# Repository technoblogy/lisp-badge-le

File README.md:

# Lisp Badge LE
A self-contained low-power computer with its own display and keyboard that you can program in Lisp. It now includes autocomplete, together with the new features in uLisp Release 4.8f.

The files are as follows:

* LispBadgeLE.ino - the uLisp source file for the Lisp Badge LE.
* LispBadgeLE-comments.ino - identical but including comprehensive comments.

Only use one of these files. It should be compiled and uploaded using the Arduino IDE.

For more information see http://www.technoblogy.com/show?3Z2Y.

Note that for consistency with the previous version of the Lisp Badge LE, autocomplete has been assigned to **META-ESC**. If you think that it would be more convenient to have autocomplete on **ESC** and Escape on **META-ESC**, swap the occurrences of '\e' and '\t' in **Keymap[]** before uploading uLisp.

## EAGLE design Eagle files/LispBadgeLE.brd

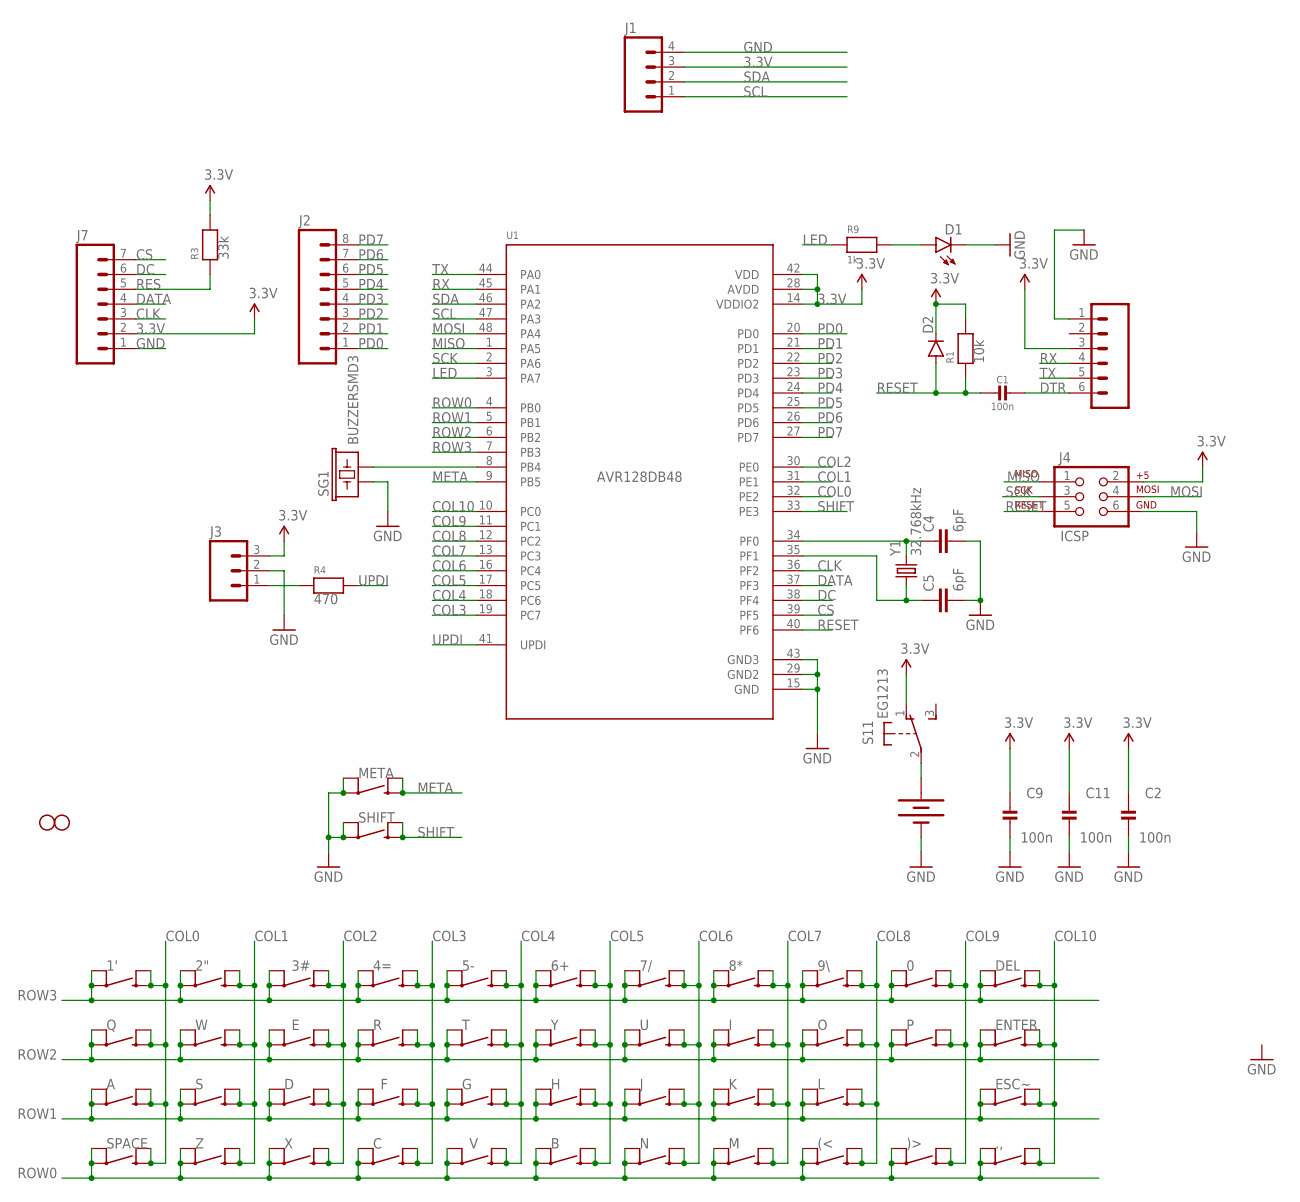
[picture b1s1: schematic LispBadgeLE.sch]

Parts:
0, 1', 2", 3#, 4=, 5-, 6+, 7/, 8*, 9\\, .,: SWITCH-MOMENTARY-2SMD-4; TACTILE_SWITCH_TALL
(<: SWITCH-MOMENTARY-2SMD-4; TACTILE_SWITCH_TALL
)>: SWITCH-MOMENTARY-2SMD-4; TACTILE_SWITCH_TALL
A: SWITCH-MOMENTARY-2SMD-4; TACTILE_SWITCH_TALL
B: SWITCH-MOMENTARY-2SMD-4; TACTILE_SWITCH_TALL
BAT1: 20mm coincell; BATTCON_20MM_4LEGS
C: SWITCH-MOMENTARY-2SMD-4; TACTILE_SWITCH_TALL
C1, C2, C9, C11: 100n; _0805MP
C4, C5: 6pF; 0805
D: SWITCH-MOMENTARY-2SMD-4; TACTILE_SWITCH_TALL
D1: LED1206-BOTTOM; LED-1206-BOTTOM
D2: DIODESOD123; SOD-123
DEL: SWITCH-MOMENTARY-2SMD-4; TACTILE_SWITCH_TALL
E: SWITCH-MOMENTARY-2SMD-4; TACTILE_SWITCH_TALL
ENTER: SWITCH-MOMENTARY-2SMD-4; TACTILE_SWITCH_TALL
ESC~: SWITCH-MOMENTARY-2SMD-4; TACTILE_SWITCH_TALL
F: SWITCH-MOMENTARY-2SMD-4; TACTILE_SWITCH_TALL
G: SWITCH-MOMENTARY-2SMD-4; TACTILE_SWITCH_TALL
H: SWITCH-MOMENTARY-2SMD-4; TACTILE_SWITCH_TALL
I: SWITCH-MOMENTARY-2SMD-4; TACTILE_SWITCH_TALL
J: SWITCH-MOMENTARY-2SMD-4; TACTILE_SWITCH_TALL
J1: M04LONGPADS; 1X04_LONGPADS
J2: M08LONGPADS; 1X08_LONGPADS
J3: M03LONGPADS; 1X03_LONGPADS
J4: ICSP; 2X3
J7: M07; 1X07
JP1: M06LONGPADS; 1X06_LONGPADS
JP4, JP5: STAND-OFF
K: SWITCH-MOMENTARY-2SMD-4; TACTILE_SWITCH_TALL
L: SWITCH-MOMENTARY-2SMD-4; TACTILE_SWITCH_TALL
M: SWITCH-MOMENTARY-2SMD-4; TACTILE_SWITCH_TALL
META: SWITCH-MOMENTARY-2SMD-4; TACTILE_SWITCH_TALL
N: SWITCH-MOMENTARY-2SMD-4; TACTILE_SWITCH_TALL
O: SWITCH-MOMENTARY-2SMD-4; TACTILE_SWITCH_TALL
P: SWITCH-MOMENTARY-2SMD-4; TACTILE_SWITCH_TALL
Q: SWITCH-MOMENTARY-2SMD-4; TACTILE_SWITCH_TALL
R: SWITCH-MOMENTARY-2SMD-4; TACTILE_SWITCH_TALL
R1: 10k; _0805MP
R3: 33k; _0805MP
R4: 470; _0805MP
R9: 1k; _0805MP
S: SWITCH-MOMENTARY-2SMD-4; TACTILE_SWITCH_TALL
S1: EG1213
SG1: BUZZERSMD3; BUZZER-CMT1102
SHIFT: SWITCH-MOMENTARY-2SMD-4; TACTILE_SWITCH_TALL
SPACE: SWITCH-MOMENTARY-2SMD-4; TACTILE_SWITCH_TALL
T: SWITCH-MOMENTARY-2SMD-4; TACTILE_SWITCH_TALL
U: SWITCH-MOMENTARY-2SMD-4; TACTILE_SWITCH_TALL
U1: AVR128DB48; LQFP48
V: SWITCH-MOMENTARY-2SMD-4; TACTILE_SWITCH_TALL
W: SWITCH-MOMENTARY-2SMD-4; TACTILE_SWITCH_TALL
X: SWITCH-MOMENTARY-2SMD-4; TACTILE_SWITCH_TALL
Y: SWITCH-MOMENTARY-2SMD-4; TACTILE_SWITCH_TALL
Y1: 32.768kHz; CRYSTAL-SMD-3.2X1.5MM
Z: SWITCH-MOMENTARY-2SMD-4; TACTILE_SWITCH_TALL

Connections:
3.3V: C2.1, C9.1, C11.1, D2.C, J1.3, J3.3, J4.2, J7.2, JP1.3, R1.2, R3.2, S1.1 (O), U1.14 (VDDIO2), U1.28 (AVDD), U1.42 (VDD)
CLK: J7.3, U1.36 (PF2)
COL0: 1'.B1 (4), 1'.B2 (2), A.B1 (4), A.B2 (2), Q.B1 (4), Q.B2 (2), SPACE.B1 (4), SPACE.B2 (2), U1.32 (PE2)
COL1: 2".B1 (4), 2".B2 (2), S.B1 (4), S.B2 (2), U1.31 (PE1), W.B1 (4), W.B2 (2), Z.B1 (4), Z.B2 (2)
COL2: 3#.B1 (4), 3#.B2 (2), D.B1 (4), D.B2 (2), E.B1 (4), E.B2 (2), U1.30 (PE0), X.B1 (4), X.B2 (2)
COL3: 4=.B1 (4), 4=.B2 (2), C.B1 (4), C.B2 (2), F.B1 (4), F.B2 (2), R.B1 (4), R.B2 (2), U1.19 (PC7)
COL4: 5-.B1 (4), 5-.B2 (2), G.B1 (4), G.B2 (2), T.B1 (4), T.B2 (2), U1.18 (PC6), V.B1 (4), V.B2 (2)
COL5: 6+.B1 (4), 6+.B2 (2), B.B1 (4), B.B2 (2), H.B1 (4), H.B2 (2), U1.17 (PC5), Y.B1 (4), Y.B2 (2)
COL6: 7/.B1 (4), 7/.B2 (2), J.B1 (4), J.B2 (2), N.B1 (4), N.B2 (2), U.B1 (4), U.B2 (2), U1.16 (PC4)
COL7: 8*.B1 (4), 8*.B2 (2), I.B1 (4), I.B2 (2), K.B1 (4), K.B2 (2), M.B1 (4), M.B2 (2), U1.13 (PC3)
COL8: 9\\.B1 (4), 9\\.B2 (2), (<.B1 (4), (<.B2 (2), L.B1 (4), L.B2 (2), O.B1 (4), O.B2 (2), U1.12 (PC2)
COL9: 0.B1 (4), 0.B2 (2), )>.B1 (4), )>.B2 (2), P.B1 (4), P.B2 (2), U1.11 (PC1)
COL10: .,.B1 (4), .,.B2 (2), DEL.B1 (4), DEL.B2 (2), ENTER.B1 (4), ENTER.B2 (2), ESC~.B1 (4), ESC~.B2 (2), U1.10 (PC0)
CS: J7.7, U1.39 (PF5)
DATA: J7.4, U1.37 (PF3)
DC: J7.6, U1.38 (PF4)
DTR: C1.1, JP1.6
GND: BAT1.NEGATIVE (-), C2.2, C4.2, C5.2, C9.2, C11.2, D1.C, J1.4, J3.2, J4.6, J7.1, JP1.1, META.A1 (3), META.A2 (1), SG1.1, SHIFT.A1 (3), SHIFT.A2 (1), U1.15 (GND), U1.29 (GND2), U1.43 (GND3)
LED: R9.1, U1.3 (PA7)
META: META.B1 (4), META.B2 (2), U1.9 (PB5)
MISO: J4.1, U1.1 (PA5)
MOSI: J4.4, U1.48 (PA4)
unnamed: C5.1, U1.35 (PF1), Y1.P$1 (1)
unnamed: C4.1, U1.34 (PF0), Y1.P$2 (2)
unnamed: D1.A, R9.2
unnamed: BAT1.POSITIVE@1 (+), BAT1.POSITIVE@2 (+), BAT1.POSITIVE@3 (+), BAT1.POSITIVE@4 (+), S1.2
unnamed: SG1.2, U1.8 (PB4)
unnamed: J3.1, R4.1
PD0: J2.1, U1.20 (PD0)
PD1: J2.2, U1.21 (PD1)
PD2: J2.3, U1.22 (PD2)
PD3: J2.4, U1.23 (PD3)
PD4: J2.5, U1.24 (PD4)
PD5: J2.6, U1.25 (PD5)
PD6: J2.7, U1.26 (PD6)
PD7: J2.8, U1.27 (PD7)
RES: J7.5, R3.1
RESET: C1.2, D2.A, J4.5, R1.1, U1.40 (PF6)
ROW0: (<.A1 (3), (<.A2 (1), )>.A1 (3), )>.A2 (1), .,.A1 (3), .,.A2 (1), B.A1 (3), B.A2 (1), C.A1 (3), C.A2 (1), M.A1 (3), M.A2 (1), N.A1 (3), N.A2 (1), SPACE.A1 (3), SPACE.A2 (1), U1.4 (PB0), V.A1 (3), V.A2 (1), X.A1 (3), X.A2 (1), Z.A1 (3), Z.A2 (1)
ROW1: A.A1 (3), A.A2 (1), D.A1 (3), D.A2 (1), ESC~.A1 (3), ESC~.A2 (1), F.A1 (3), F.A2 (1), G.A1 (3), G.A2 (1), H.A1 (3), H.A2 (1), J.A1 (3), J.A2 (1), K.A1 (3), K.A2 (1), L.A1 (3), L.A2 (1), S.A1 (3), S.A2 (1), U1.5 (PB1)
ROW2: E.A1 (3), E.A2 (1), ENTER.A1 (3), ENTER.A2 (1), I.A1 (3), I.A2 (1), O.A1 (3), O.A2 (1), P.A1 (3), P.A2 (1), Q.A1 (3), Q.A2 (1), R.A1 (3), R.A2 (1), T.A1 (3), T.A2 (1), U.A1 (3), U.A2 (1), U1.6 (PB2), W.A1 (3), W.A2 (1), Y.A1 (3), Y.A2 (1)
ROW3: 0.A1 (3), 0.A2 (1), 1'.A1 (3), 1'.A2 (1), 2".A1 (3), 2".A2 (1), 3#.A1 (3), 3#.A2 (1), 4=.A1 (3), 4=.A2 (1), 5-.A1 (3), 5-.A2 (1), 6+.A1 (3), 6+.A2 (1), 7/.A1 (3), 7/.A2 (1), 8*.A1 (3), 8*.A2 (1), 9\\.A1 (3), 9\\.A2 (1), DEL.A1 (3), DEL.A2 (1), U1.7 (PB3)
RX: JP1.4, U1.45 (PA1)
SCK: J4.3, U1.2 (PA6)
SCL: J1.1, U1.47 (PA3)
SDA: J1.2, U1.46 (PA2)
SHIFT: SHIFT.B1 (4), SHIFT.B2 (2), U1.33 (PE3)
TX: JP1.5, U1.44 (PA0)
UPDI: R4.2, U1.41 (UPDI)

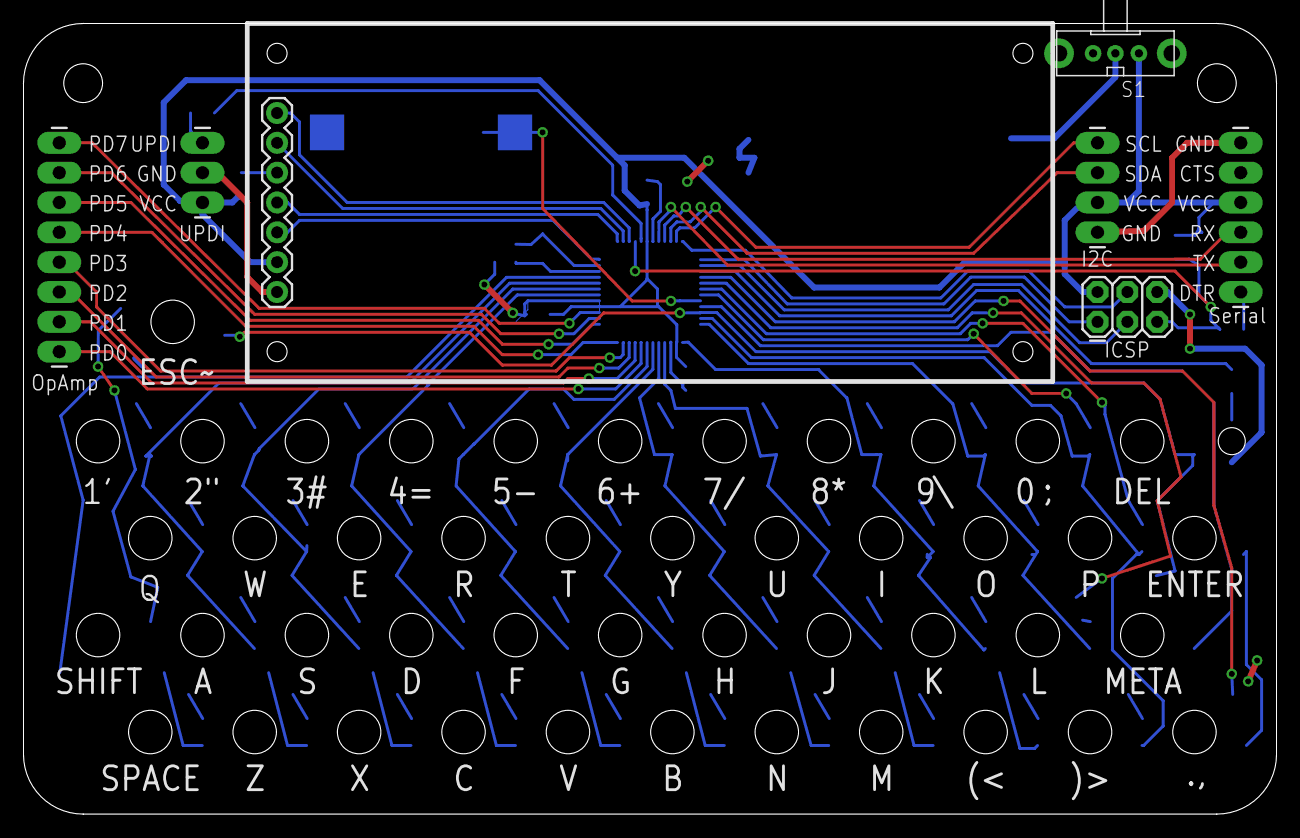
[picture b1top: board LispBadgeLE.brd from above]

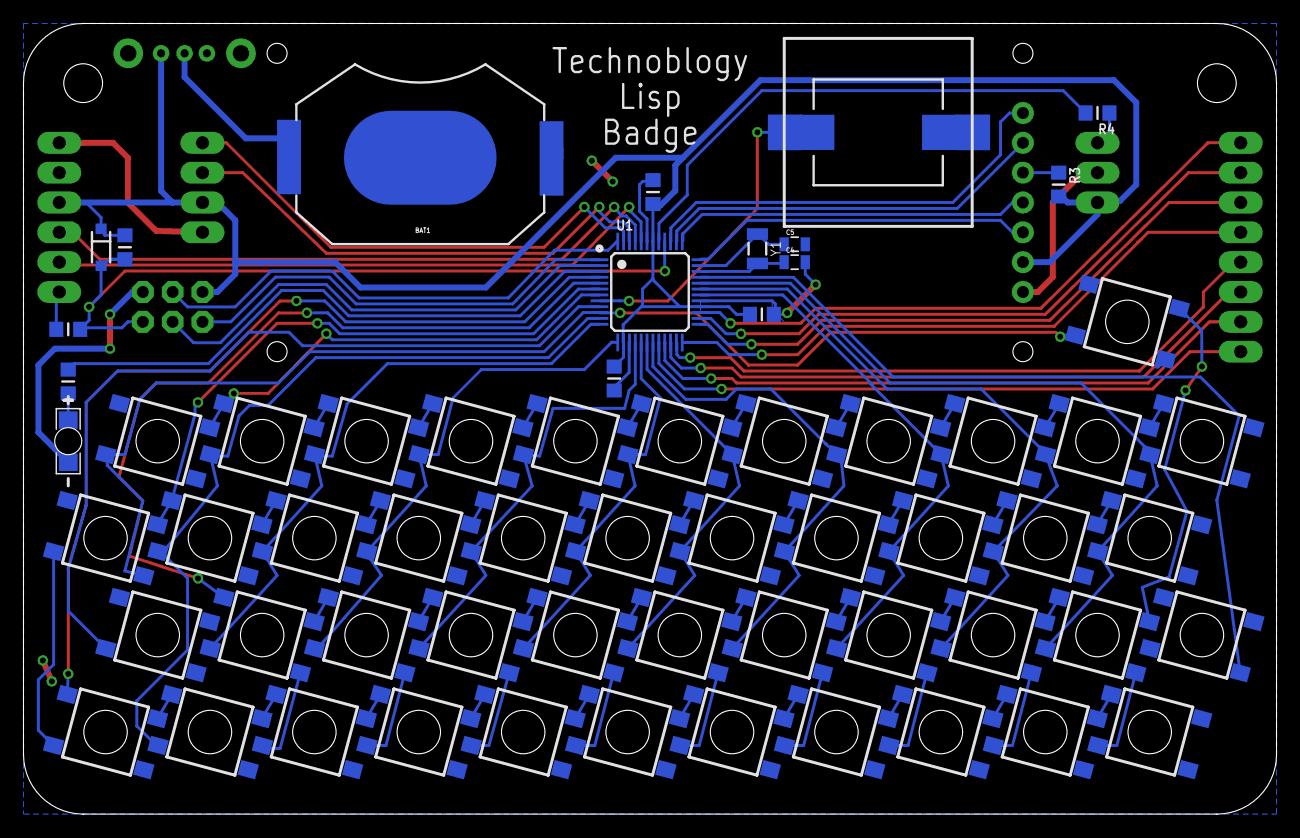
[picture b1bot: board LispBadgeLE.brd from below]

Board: 2 copper layers, 106.7 x 67.3 mm, 70 parts (61 on the bottom side), 49 nets.

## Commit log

2023-09-27 Release 1 - 27th September 2023
2024-03-05 Release 2 - 5th March 2024
2024-06-25 Release 3 - 25th June 2024
    Updated to uLisp Release 4.6
2025-11-10 Version 4 - 9th November 2025
    uLisp Release 4.8f

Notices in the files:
parts and their libraries:
SparkFun-Electromechanical: Licensing: Creative Commons ShareAlike 4.0 International - https://creativecommons.org/licenses/by-sa/4.0
SparkFun-Connectors: Licensing: CC v3.0 Share-Alike You are welcome to use this library for commercial purposes.
